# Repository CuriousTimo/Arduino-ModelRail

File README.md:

# Code for all kinds of LocoNet and DCC devices using an Arduino

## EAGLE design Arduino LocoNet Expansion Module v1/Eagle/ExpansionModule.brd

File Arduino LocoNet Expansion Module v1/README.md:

# Arduino LocoNet Expansion Module v1

A general-purpose expansion for the [Arduino Nano LocoNet & DCC Interface v3](../Arduino%20LocoNet-DCC%20Interface%20v3) (or a v2 with the [v2 Expansion Adapter](../Arduino%20LocoNet-DCC%20v2%20Expansion%20Adapter)). It connects with two 10-pin flat cables to **EXP1** and **EXP2** and brings sixteen Nano pins out to screw terminals, **P1 to P16**, plus 5 V and GND terminals.

The board is made for different setups: **you only fit the parts your project needs**, chosen per terminal. A terminal can be a plain connection to the Nano pin (for an output, a button, a servo signal) or a protected input (for Märklin contact tracks or reed contacts), and one board can mix both.

Designed in EAGLE 9.6.2: the schematic and the board are in [`Eagle/`](Eagle), the Gerber files (31 January 2021) for ordering the board in [`Gerber/`](Gerber). Board 65.7 × 83.8 mm, two layers, through-hole parts only.

*The board from above, drawn from the EAGLE file: red tracks on top, blue underneath, green pads, grey the printing on the board.*

## Fitting the board for your task

Every terminal has the same places for parts. Choose for each terminal:

| Use | Fit | Leave empty |
| --- | --- | --- |
| **Plain connection**: an output (an LED with its own resistor, a servo signal), a sensor with a 5 V output | Jumper **JP** closed, or a wire bridge in its place | R, 1N4148, 1N4004, C |
| **Switch input**: a push button, toggle switch, reed contact or turnout end switch to GND | 1 kΩ **R**, **1N4148**, **1N4004**, **C** | JP (open) |
| **3-rail feedback**: a Märklin contact track (isolated outer rail), also with a DCC command station such as the Intellibox | 1 kΩ **R**, **1N4148**, **1N4004**, **C** | JP (open) |
| **Not used** | Nothing | Everything |

Fit the **terminals** you use and the **EXP** headers for the cables you need: EXP1 for P1 to P8, EXP2 for P9 to P16. The 5V and GND terminals only when something needs power from the board.

## Switch input and 3-rail feedback

Both use the same parts, and one board can have both. The full circuit of one terminal, with all its parts fitted:

```text
 Nano pin ──┬── 1 kΩ ──▶|── 1N4148 ──┬── terminal P
            │                         │
           C                       1N4004
            │                       (▲ to GND)
           GND                        │
                                     GND
     and jumper JP: Nano pin ── terminal P (bypasses the resistor and diode)
```

- The Nano pin is an input with its **internal pull-up** switched on (`pinMode(pin, INPUT_PULLUP)`).
- **Nothing connected, or the contact open:** the pin reads **HIGH**.
- **Terminal connected to GND** (a pressed button, a closed reed contact): current flows through the 1 kΩ and the 1N4148, and the pin reads **LOW**.
- **The 1N4148** keeps positive voltages on the terminal away from the Nano, for example when a wire touches the track or the 16 V lighting supply.
- **The 1N4004** takes negative voltages on the terminal to GND.
- **The capacitor** filters short spikes and contact bounce. Its value is not in the design; 100 nF is the usual choice.

### Switch input

Connect the switch between the terminal and a **GND** terminal. Closed is LOW, open is HIGH.

### 3-rail feedback with the diode trick

On a Märklin contact track, one outer rail is cut on both sides of the section and wired to the terminal. A train's metal wheels connect it to the other outer rail.

- **With a Märklin system** (the outer rails are the track's ground, brown "0") and the board's GND connected to that ground, it works like a switch: a train pulls the terminal to GND, and the pin reads LOW.
- **With a DCC command station or booster** (such as the Intellibox), the outer rails are not ground: they switch between 0 V and the full track voltage thousands of times a second. This is where the **diode trick** comes in:
  - In the half where the rail is at 0 V, the 1N4148 conducts and pulls the pin LOW.
  - In the half where the rail is at track voltage, the 1N4148 blocks, so the Nano never sees the track voltage.
  - The capacitor holds the pin LOW until the next 0 V half, so the pin stays LOW as long as a train is on the section.
  
  The board's GND must share a ground with the command station; through LocoNet it normally does. Test one section with a loco before wiring the whole layout.

Dirty wheels and track make the contact flicker. Let the program wait about half a second after the last LOW before it reports the section as free.

**Jumper JP1 to JP16** (one per terminal, next to it) connects the Nano pin straight to the terminal, without the protection: the plain connection. Then the terminal is not protected, so never more than 5 V on it, and leave the capacitor out on outputs (it would slow down a servo signal).

## Terminals and Nano pins

| Terminal | Nano pin | Flat cable | | Terminal | Nano pin | Flat cable |
| --- | --- | --- | --- | --- | --- | --- |
| P1 | D2 | EXP1 pin 1 | | P9 | D12 | EXP2 pin 1 |
| P2 | D3 | EXP1 pin 2 | | P10 | D13 | EXP2 pin 2 |
| P3 | D4 | EXP1 pin 3 | | P11 | A0 | EXP2 pin 3 |
| P4 | D5 | EXP1 pin 4 | | P12 | A1 | EXP2 pin 4 |
| P5 | D6 | EXP1 pin 5 | | P13 | A2 | EXP2 pin 5 |
| P6 | D9 | EXP1 pin 6 | | P14 | A3 | EXP2 pin 6 |
| P7 | D10 | EXP1 pin 7 | | P15 | SDA (A4) | EXP2 pin 7 |
| P8 | D11 | EXP1 pin 8 | | P16 | SCL (A5) | EXP2 pin 8 |

Pins 9 and 10 of both flat cables are 5 V and GND. The two **5V** and two **GND** terminals on the left (top and bottom) carry them, for example to power IR or Hall sensors.

Some inputs share their Nano pin with something on the interface board:

| Terminal | Shared with | What to do |
| --- | --- | --- |
| **P1** (D2) | The DCC input | Leave P1 unused when the interface's DCC part (6N137) is fitted |
| **P4, P5** (D5, D6) | The interface's blue terminal, when its SCL/SDA jumpers are on the right | Put those jumpers on the left, or leave the blue terminal's D5/D6 unused |
| **P10** (D13) | The Nano's own LED on D13 | The LED pulls the pin down, so the pull-up does not work reliably; use P10 as an output, or leave it unused |
| **P15, P16** (A4, A5) | I2C | Not available as inputs when I2C is used (a PCA9685, the Märklin I2C Expansion). The interface's "i2c pullup" jumper may stay on; it only makes the pull-up stronger |

D0, D1 (USB) and D7, D8 (LocoNet) are not on the flat cables.

## Parts list

Fit only what you need (see [Fitting the board for your task](#fitting-the-board-for-your-task)). Per terminal:

| Part | Value | For |
| --- | --- | --- |
| R | 1 kΩ | Protected input |
| D (small glass diode) | 1N4148 | Protected input |
| D (larger black diode) | 1N4004 | Protected input |
| C | 100 nF (value not in the design), 5 mm pin spacing | Protected input |
| JP | 2-pin header and a jumper, or a wire bridge | Plain connection |

For the board:

| Part | Value | Number |
| --- | --- | --- |
| PORT1 to PORT8 | 2-pole terminal, 5.08 mm (each holds two terminals, for example P1 and P2) | 1 to 8, as needed |
| 5V-L, 5V-R, GND-L, GND-R | 2-pole terminal, 5.08 mm | As needed |
| EXP1, EXP2 | 10-pin boxed header (2 × 5, 2.54 mm) | 1 or 2 |
| | 10-pin flat cable with two connectors | 1 or 2 |

A board with all sixteen protected inputs needs 16 of each: R1 to R16, sixteen 1N4148, sixteen 1N4004 and C1 to C16.

## Software

No program in this repository uses the module yet. Reading an input in an Arduino sketch:

```cpp
const uint8_t kInputs[16] = {2, 3, 4, 5, 6, 9, 10, 11, 12, 13, A0, A1, A2, A3, A4, A5};  // P1 to P16

void setup() {
  for (uint8_t pin : kInputs) pinMode(pin, INPUT_PULLUP);
}

void loop() {
  bool occupied = digitalRead(kInputs[2]) == LOW;  // P3: LOW when the contact is closed
}
```

To report the inputs on LocoNet, send an `OPC_INPUT_REP` (sensor message) when an input changes, as LocoNet occupancy detectors do.

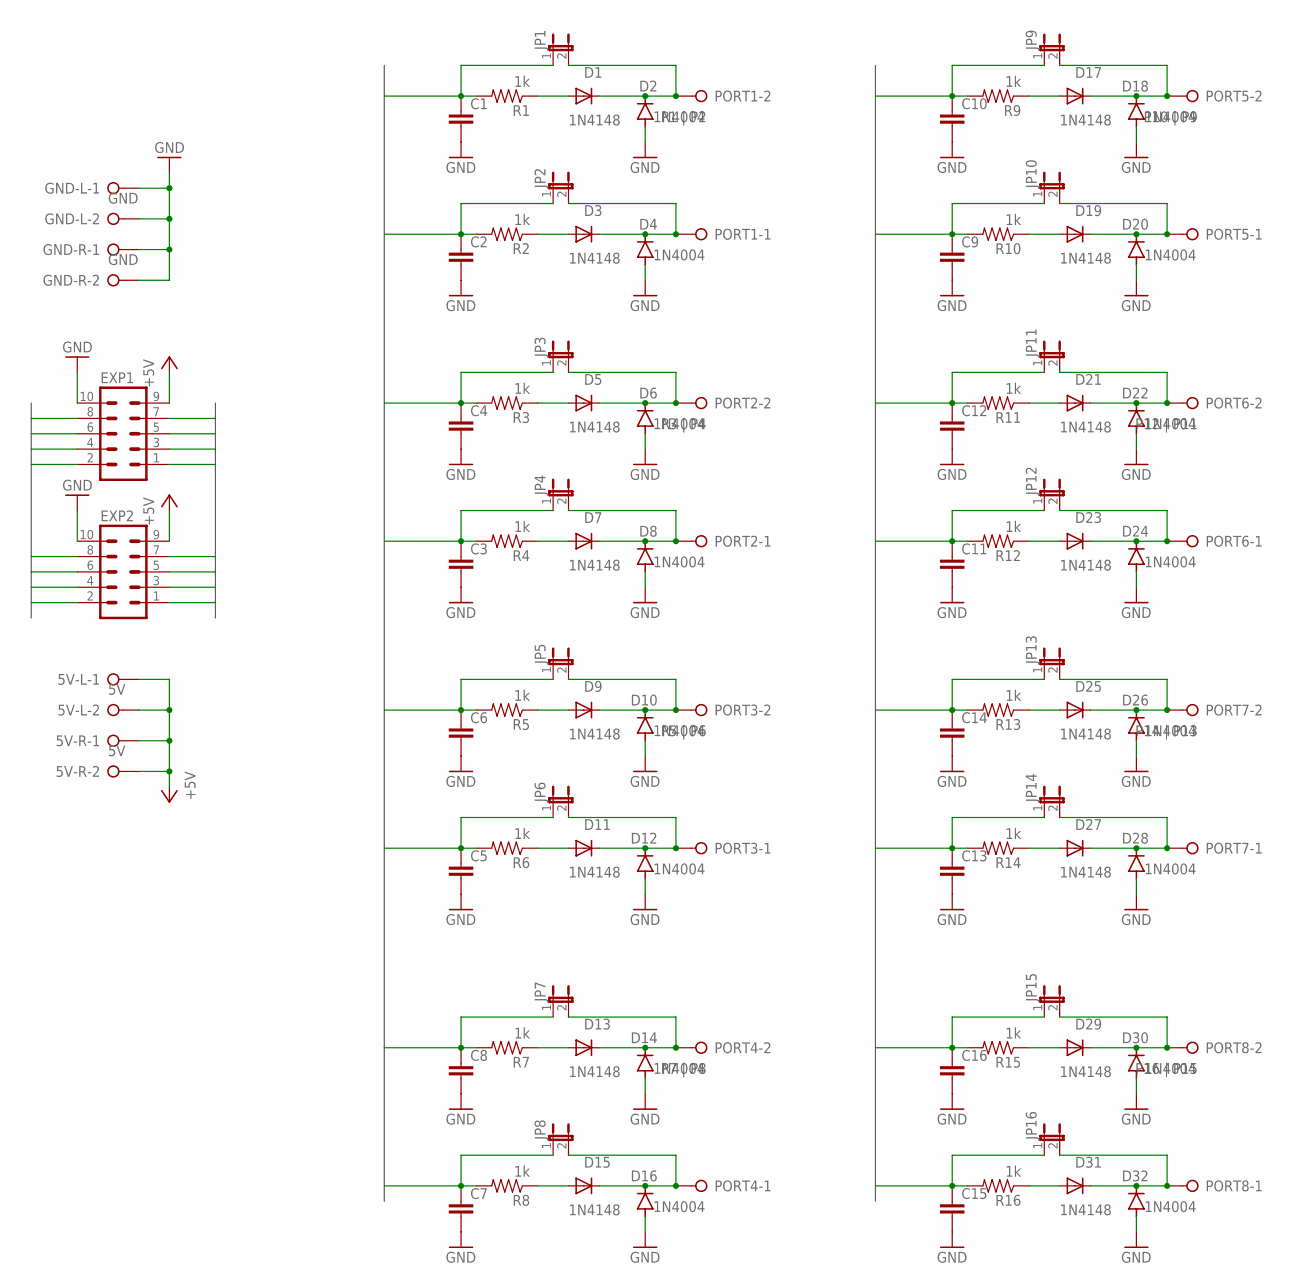
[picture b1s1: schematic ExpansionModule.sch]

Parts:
5V-L, 5V-R: 5V; W237-132
C1, C2, C3, C4, C5, C6, C7, C8, C9, C10, C11, C12, C13, C14, C15, C16: C-EU050-030X075; C050-030X075
D1, D3, D5, D7, D9, D11, D13, D15, D17, D19, D21, D23, D25, D27, D29, D31: 1N4148; DO35-7
D2, D4, D6, D8, D10, D12, D14, D16, D18, D20, D22, D24, D26, D28, D30, D32: 1N4004; DO41-10
EXP1, EXP2: ML10
GND-L: GND; W237-132
GND-R: GND; W237-132
JP1, JP2, JP3, JP4, JP5, JP6, JP7, JP8, JP9, JP10, JP11, JP12, JP13, JP14, JP15, JP16: JP1E; JP1
PORT1: P1 | P2; W237-132
PORT2: P3 | P4; W237-132
PORT3: P5 | P6; W237-132
PORT4: P7 | P8; W237-132
PORT5: P10 | P9; W237-132
PORT6: P12 | P11; W237-132
PORT7: P14 | P13; W237-132
PORT8: P16 | P15; W237-132
R1, R2, R3, R4, R5, R6, R7, R8, R9, R10, R11, R12, R13, R14, R15, R16: 1k; AXIAL-0.3

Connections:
+5V: 5V-L.1, 5V-L.2, 5V-R.1, 5V-R.2, EXP1.9, EXP2.9
A0: C12.1, EXP2.3, JP11.1, R11.P$2 (2)
A1: C11.1, EXP2.4, JP12.1, R12.P$2 (2)
A2: C14.1, EXP2.5, JP13.1, R13.P$2 (2)
A3: C13.1, EXP2.6, JP14.1, R14.P$2 (2)
GND: C1.2, C2.2, C3.2, C4.2, C5.2, C6.2, C7.2, C8.2, C9.2, C10.2, C11.2, C12.2, C13.2, C14.2, C15.2, C16.2, D2.A, D4.A, D6.A, D8.A, D10.A, D12.A, D14.A, D16.A, D18.A, D20.A, D22.A, D24.A, D26.A, D28.A, D30.A, D32.A, EXP1.10, EXP2.10, GND-L.1, GND-L.2, GND-R.1, GND-R.2
unnamed: D1.A, R1.P$1 (1)
unnamed: D3.A, R2.P$1 (1)
unnamed: D5.A, R3.P$1 (1)
unnamed: D7.A, R4.P$1 (1)
unnamed: D9.A, R5.P$1 (1)
unnamed: D11.A, R6.P$1 (1)
unnamed: D13.A, R7.P$1 (1)
unnamed: D15.A, R8.P$1 (1)
unnamed: D17.A, R9.P$1 (1)
unnamed: D19.A, R10.P$1 (1)
unnamed: D21.A, R11.P$1 (1)
unnamed: D23.A, R12.P$1 (1)
unnamed: D25.A, R13.P$1 (1)
unnamed: D27.A, R14.P$1 (1)
unnamed: D29.A, R15.P$1 (1)
unnamed: D31.A, R16.P$1 (1)
PIN2: C1.1, EXP1.1, JP1.1, R1.P$2 (2)
PIN3: C2.1, EXP1.2, JP2.1, R2.P$2 (2)
PIN4: C4.1, EXP1.3, JP3.1, R3.P$2 (2)
PIN5: C3.1, EXP1.4, JP4.1, R4.P$2 (2)
PIN6: C6.1, EXP1.5, JP5.1, R5.P$2 (2)
PIN9: C5.1, EXP1.6, JP6.1, R6.P$2 (2)
PIN10: C8.1, EXP1.7, JP7.1, R7.P$2 (2)
PIN11: C7.1, EXP1.8, JP8.1, R8.P$2 (2)
PIN12: C10.1, EXP2.1, JP9.1, R9.P$2 (2)
PIN13: C9.1, EXP2.2, JP10.1, R10.P$2 (2)
PORT1: D1.C, D2.C, JP1.2, PORT1.2
PORT2: D3.C, D4.C, JP2.2, PORT1.1
PORT3: D5.C, D6.C, JP3.2, PORT2.2
PORT4: D7.C, D8.C, JP4.2, PORT2.1
PORT5: D9.C, D10.C, JP5.2, PORT3.2
PORT6: D11.C, D12.C, JP6.2, PORT3.1
PORT7: D13.C, D14.C, JP7.2, PORT4.2
PORT8: D15.C, D16.C, JP8.2, PORT4.1
PORT9: D17.C, D18.C, JP9.2, PORT5.2
PORT10: D19.C, D20.C, JP10.2, PORT5.1
PORT11: D21.C, D22.C, JP11.2, PORT6.2
PORT12: D23.C, D24.C, JP12.2, PORT6.1
PORT13: D25.C, D26.C, JP13.2, PORT7.2
PORT14: D27.C, D28.C, JP14.2, PORT7.1
PORT15: D29.C, D30.C, JP15.2, PORT8.2
PORT16: D31.C, D32.C, JP16.2, PORT8.1
SCL: C15.1, EXP2.8, JP16.1, R16.P$2 (2)
SDA: C16.1, EXP2.7, JP15.1, R15.P$2 (2)

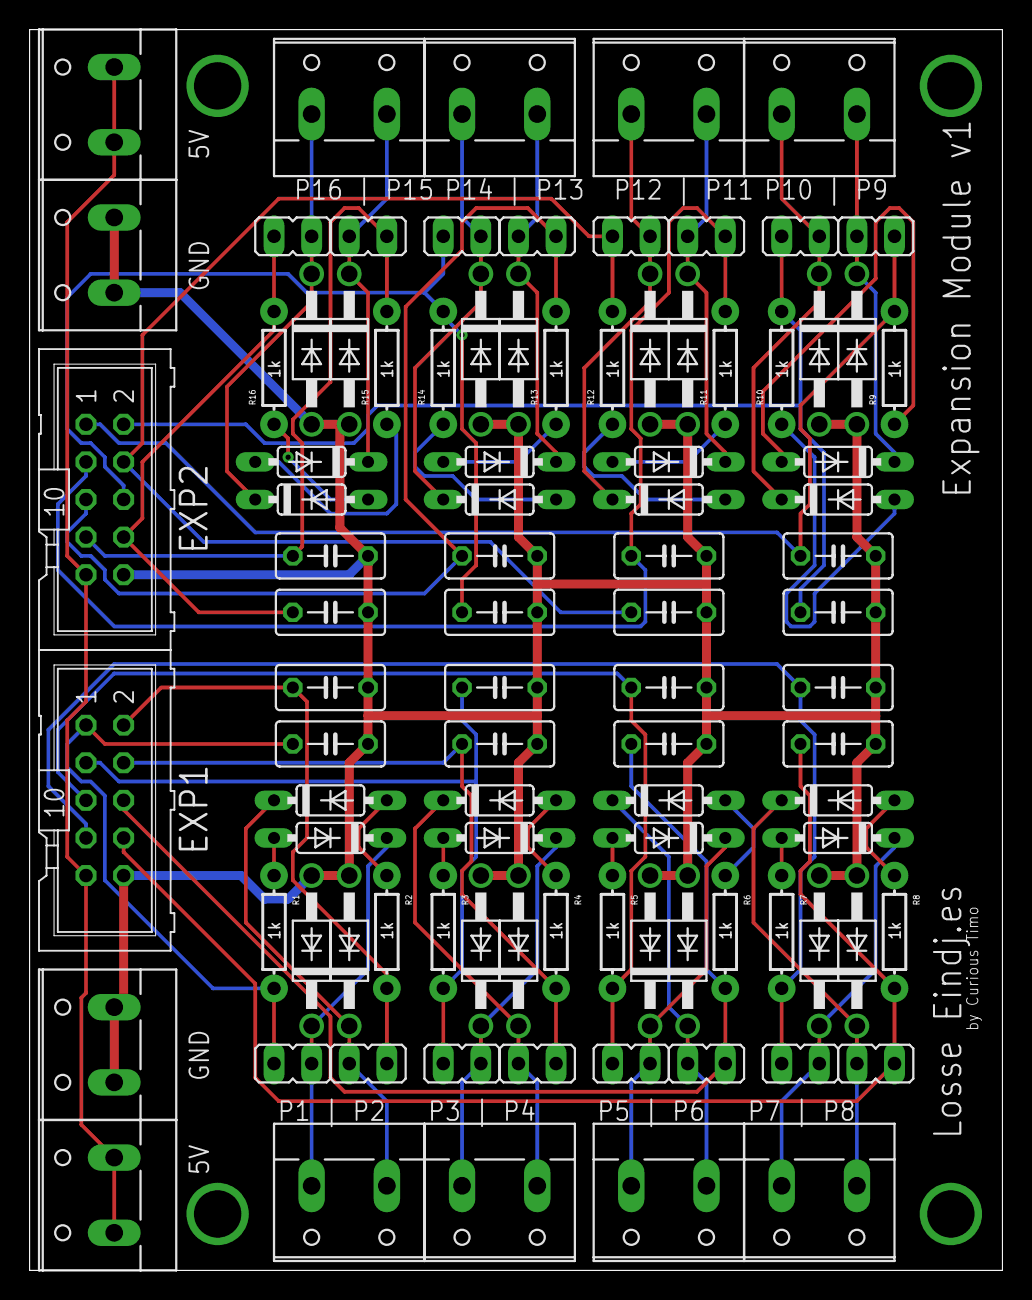
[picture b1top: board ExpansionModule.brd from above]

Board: 2 copper layers, 65.7 x 83.8 mm, 94 parts (0 on the bottom side), 50 nets.

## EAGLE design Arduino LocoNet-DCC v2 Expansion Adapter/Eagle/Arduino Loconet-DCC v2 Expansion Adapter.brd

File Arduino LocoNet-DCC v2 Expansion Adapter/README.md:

# Arduino LocoNet-DCC v2 Expansion Adapter

Gives an [Arduino Nano LocoNet & DCC Interface v2](../Arduino%20LocoNet-DCC%20Interface%20v2) the two expansion headers of the [v3](../Arduino%20LocoNet-DCC%20Interface%20v3), **EXP1** and **EXP2**, so expansion boards made for the v3 work on a v2 with the same 10-pin flat cable, for example the [Märklin I2C Expansion v1](../Marklin%20I2C%20Expansion%20v1) for [Marklin-6040-LocoNet](../Marklin-6040-LocoNet).

Designed in EAGLE 9.6.2: the schematic and the board are in [`Eagle/`](Eagle). Board 42.9 × 30.5 mm, two layers.

*The board from above, drawn from the EAGLE file: red tracks on top, blue underneath, green pads, grey the printing on the board.*

## How it fits

The adapter sits between the v2 board and the Arduino Nano:

1. Solder two **15-pin stackable headers** into the adapter (sockets on top, long pins underneath), and the two 10-pin headers EXP1 and EXP2.
2. Plug the adapter into the v2's Nano sockets, with the "<-Arduino USB" marking on the same side as the v2's.
3. Plug the Nano into the adapter.

Every Nano pin reaches the v2 board through the long pins; the adapter only takes the pins below off to the expansion headers. LocoNet (D7, D8) and the serial port (D0, D1) are not on the headers and stay free for the v2.

## Expansion headers

Wired exactly as on the v3, so a flat cable fits either board:

| Pin | EXP1 | EXP2 |
| --- | --- | --- |
| 1 | D2 (DCC input) | D12 |
| 2 | D3 | D13 |
| 3 | D4 | A0 |
| 4 | D5 | A1 |
| 5 | D6 | A2 |
| 6 | D9 | A3 |
| 7 | D10 | SDA (A4) |
| 8 | D11 | SCL (A5) |
| 9 | 5 V | 5 V |
| 10 | GND | GND |

D5 and D6 are also on the v2's blue terminal when its SCL/SDA jumpers are on the right, and SDA and SCL when they are on the left (see the [v2 jumpers](../Arduino%20LocoNet-DCC%20Interface%20v2#jumpers)); don't use the same pin on both.

## With the Märklin I2C Expansion

Connect the expansion to **EXP2**, and on the v2 put the **i2c pullup** jumper on (the Keyboard bus needs it). The rest is as described for the [Märklin I2C Expansion](../Marklin%20I2C%20Expansion%20v1).

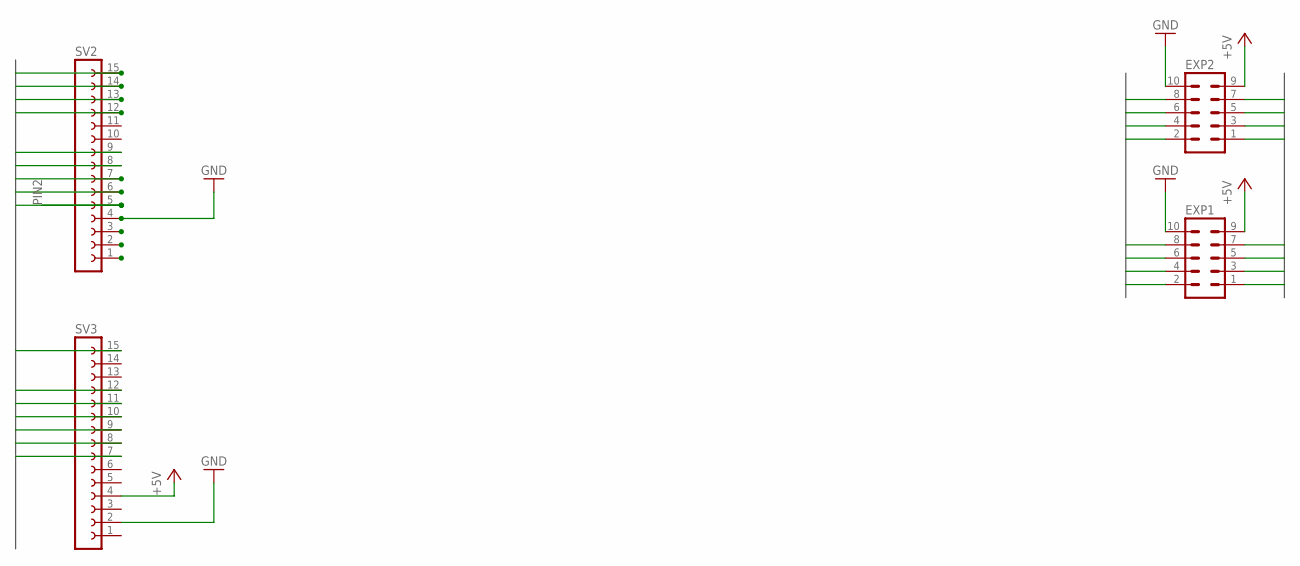
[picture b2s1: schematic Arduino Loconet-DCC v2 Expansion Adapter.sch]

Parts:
EXP1, EXP2: ML10
SV2, SV3: FE15-1NOTEXT; FE15

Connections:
+5V: EXP1.9, EXP2.9, SV3.4
A0: EXP2.3, SV3.12
A1: EXP2.4, SV3.11
A2: EXP2.5, SV3.10
A3: EXP2.6, SV3.9
GND: EXP1.10, EXP2.10, SV2.4, SV3.2
PIN2: EXP1.1, SV2.5
PIN3: EXP1.2, SV2.6
PIN4: EXP1.3, SV2.7
PIN5: EXP1.4, SV2.8
PIN6: EXP1.5, SV2.9
PIN9: EXP1.6, SV2.12
PIN10: EXP1.7, SV2.13
PIN11: EXP1.8, SV2.14
PIN12: EXP2.1, SV2.15
PIN13: EXP2.2, SV3.15
RESET: SV2.3
RXD: SV2.2
SCL: EXP2.8, SV3.7
SDA: EXP2.7, SV3.8
TXD: SV2.1

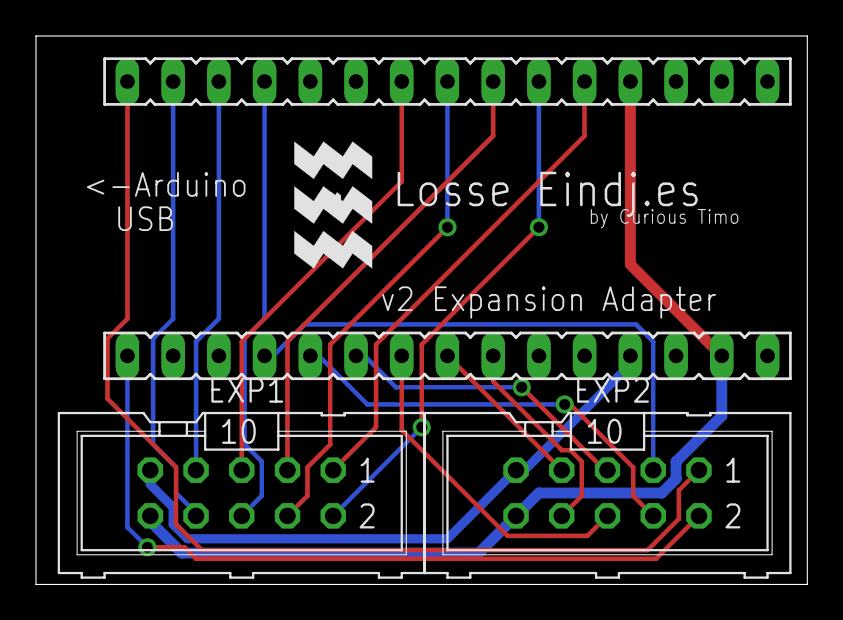
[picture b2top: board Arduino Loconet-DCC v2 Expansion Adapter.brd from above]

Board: 2 copper layers, 42.9 x 30.5 mm, 4 parts (0 on the bottom side), 18 nets.

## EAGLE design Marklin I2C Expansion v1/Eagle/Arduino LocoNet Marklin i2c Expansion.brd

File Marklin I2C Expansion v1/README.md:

# Märklin I2C Expansion v1

An expansion for the [Arduino Nano LocoNet & DCC Interface v3](../Arduino%20LocoNet-DCC%20Interface%20v3) (or a v2 with the [v2 Expansion Adapter](../Arduino%20LocoNet-DCC%20v2%20Expansion%20Adapter)) that connects Märklin Keyboards 6040 (the Märklin Digital accessory bus, I2C) to the Nano. Used by [Marklin-6040-LocoNet](../Marklin-6040-LocoNet), which makes unmodified Keyboards 6040 work on LocoNet like an Uhlenbrock IB-Switch.

Designed in EAGLE 9.6.2: the schematic and the board are in [`Eagle/`](Eagle). Board 44.8 × 61 mm, two layers.

*The board from above, drawn from the EAGLE file: red tracks on top, blue underneath, green pads, grey the printing on the board.*

## On the board

- **Two DIN 41612 connectors** (left and right, 32-pole B/2), for the Keyboards' side connectors: SDA, SCL, STOP, GO, INIT and 8 V. The left and right connectors are mirrored, so a Keyboard fits on either side, and further Keyboards plug onto each other as usual.
- **XL6009 step-up converter** that makes the Keyboards' 8 V, through a 1N4004 diode.
- **10-pin ribbon cable** to the interface board's **EXP2**: STOP to D12, GO to A0, INIT to A1, a red LED to D13, SDA and SCL to A4 and A5, plus 5 V and GND.
- **DC-IN** two-pole terminal and jumper **JP1**.

## Before switching on

1. Close the **"i2c pullup"** jumper on the interface board: the Keyboard bus needs pull-ups to 5 V.
2. Feed **DC-IN with 5 V** and leave **JP1 open**. Each Keyboard draws about 120 mA at 8 V, which is too much for the interface board's 7805 or for LocoNet.
3. **Never more than 5 V on DC-IN with JP1 closed:** JP1 connects DC-IN to the Nano's 5 V.
4. Give every Keyboard its own number with the four switches on its back (see the table in the [Marklin-6040-LocoNet README](../Marklin-6040-LocoNet#setting-up)).

## To check before building more

- **STOP, GO and INIT** go straight to Nano pins. Measure their voltage on a Keyboard bus before using them (the firmware leaves STOP and GO switched off until then).
- **JP1** connects DC-IN to the Nano's 5 V without protection; a marking on the board ("5 V only") or a diode would help.

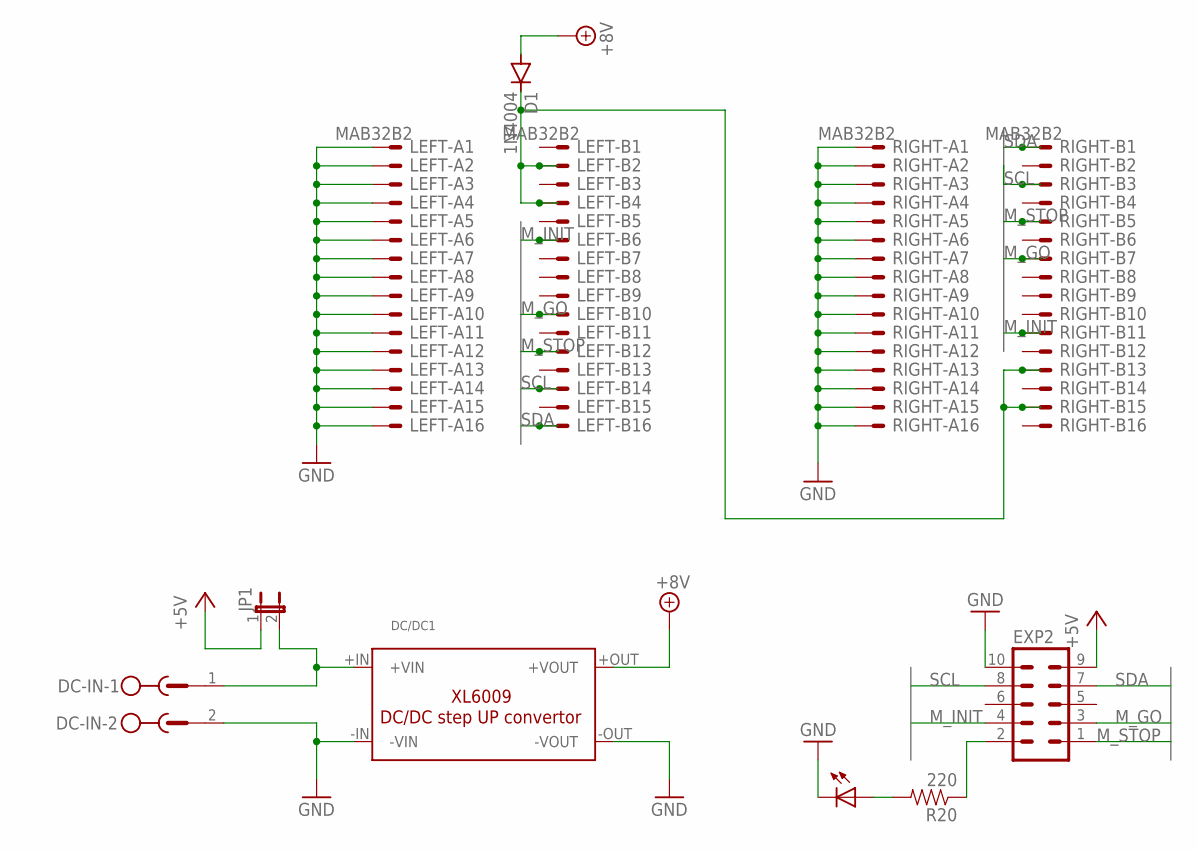
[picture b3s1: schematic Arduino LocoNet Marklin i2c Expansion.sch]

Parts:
D1: 1N4004; DO41-10
DC-IN: 2EDG-02
DC/DC1: DC/DC-STEP-UP-XL6009
EXP2: ML10
JP1: JP1E; JP1
LED: RED; LED3MM
LEFT: MAB32B2
R20: 220; AXIAL-0.3
RIGHT: MAB32B2

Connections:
+5V: EXP2.9, JP1.1
+8V: D1.A, DC/DC1.+OUT (+VOUT)
DC+: DC-IN.1, DC/DC1.+IN (+VIN), JP1.2
GND: DC-IN.2, DC/DC1.-IN (-VIN), DC/DC1.-OUT (-VOUT), EXP2.10, LED.K (C), LEFT.A1, LEFT.A2, LEFT.A3, LEFT.A4, LEFT.A5, LEFT.A6, LEFT.A7, LEFT.A8, LEFT.A9, LEFT.A10, LEFT.A11, LEFT.A12, LEFT.A13, LEFT.A14, LEFT.A15, LEFT.A16, RIGHT.A1, RIGHT.A2, RIGHT.A3, RIGHT.A4, RIGHT.A5, RIGHT.A6, RIGHT.A7, RIGHT.A8, RIGHT.A9, RIGHT.A10, RIGHT.A11, RIGHT.A12, RIGHT.A13, RIGHT.A14, RIGHT.A15, RIGHT.A16
M_GO: EXP2.3, LEFT.B10, RIGHT.B7
M_INIT: EXP2.4, LEFT.B6, RIGHT.B11
M_STOP: EXP2.1, LEFT.B12, RIGHT.B5
unnamed: LED.A, R20.P$2 (2)
unnamed: D1.C, LEFT.B2, LEFT.B4, RIGHT.B13, RIGHT.B15
PIN13: EXP2.2, R20.P$1 (1)
SCL: EXP2.8, LEFT.B14, RIGHT.B3
SDA: EXP2.7, LEFT.B16, RIGHT.B1

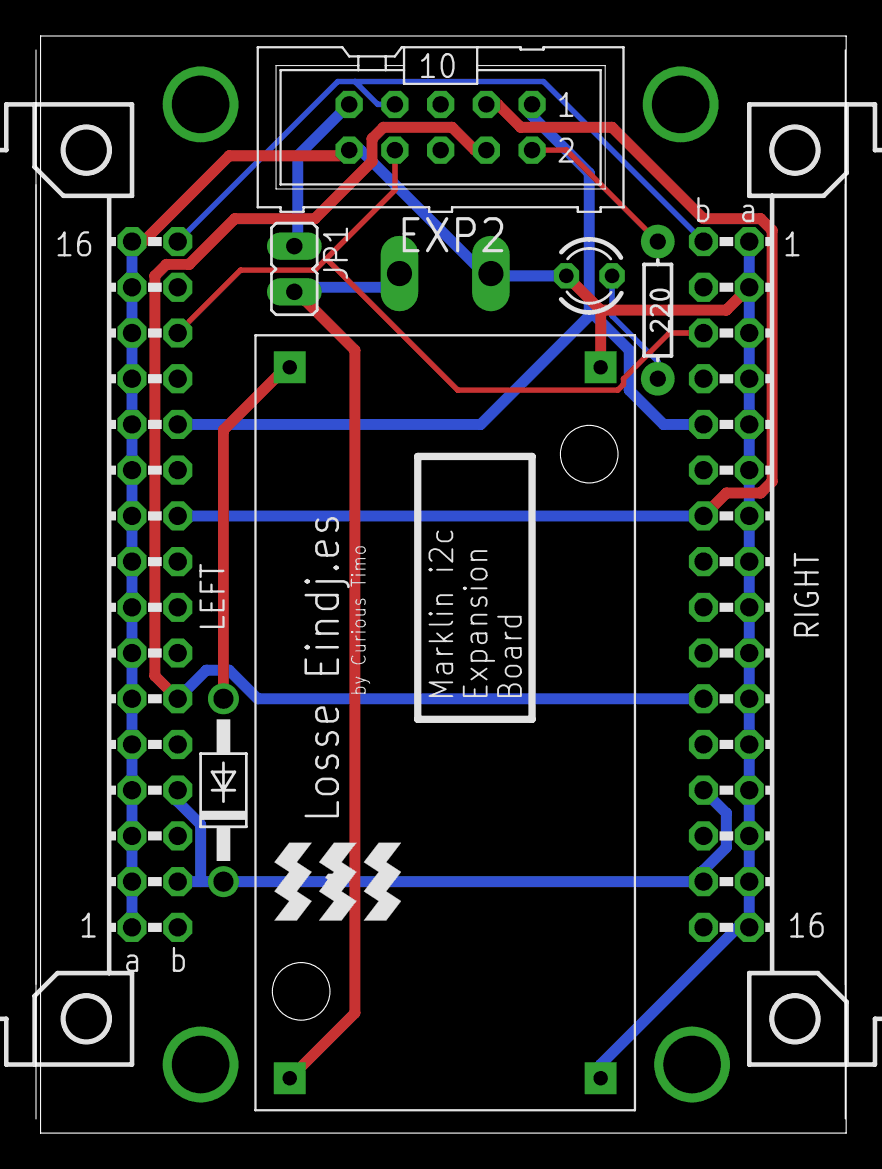
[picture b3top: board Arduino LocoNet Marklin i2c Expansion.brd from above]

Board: 2 copper layers, 44.8 x 61.0 mm, 9 parts (1 on the bottom side), 12 nets.

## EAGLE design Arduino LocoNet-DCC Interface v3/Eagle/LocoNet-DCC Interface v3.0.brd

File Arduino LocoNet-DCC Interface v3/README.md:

# Arduino Nano LocoNet & DCC Interface v3

The base module for LocoNet projects with an Arduino Nano: LocoNet in and out, a DCC input, I2C for servo drivers and expansion boards, and two expansion headers. It is the successor of the [v2](../Arduino%20LocoNet-DCC%20Interface%20v2) and the base of [Marklin-6040-LocoNet](../Marklin-6040-LocoNet), together with the [Märklin I2C Expansion v1](../Marklin%20I2C%20Expansion%20v1).

Designed in EAGLE 9.6.2: the schematic and the board are in [`Eagle/`](Eagle). Board 108.9 × 47 mm, two layers, through-hole parts only.

*The board from above, drawn from the EAGLE file: red tracks on top, blue underneath, green pads, grey the printing on the board.*

## On the board

| Part | What it does | Nano pin |
| --- | --- | --- |
| 2 × LocoNet socket (RJ12) | LocoNet in and out, wired straight through | |
| LocoNet receive | LM393 comparator: switches at about 4.5 V rising and 3.5 V falling on the LocoNet line; red LED shows LocoNet traffic | **D8** (the input-capture pin the LocoNet library needs) |
| LocoNet send | BC337 transistor that pulls the LocoNet line low | **D7** |
| DCC input | 6N137 optocoupler, DCC from the track or a booster on the two-pole terminal | **D2** (interrupt, as NmraDcc needs) |
| Power | 7805 regulator, fed from LocoNet RailSync or a separate power input (both through diodes); green LED | |
| I2C | 4.7 kΩ pull-ups (jumper), a 6-pin header for a PCA9685 servo board | A4 (SDA), A5 (SCL) |
| Blue 4-pole terminal | 5V · SCL/D5 · SDA/D6 · GND: either I2C or D5/D6, chosen with jumpers | |
| Power terminal (PWR +, GND) | A separate supply for the 7805, about 9 to 15 V DC | |
| DCC terminal | DCC from the track or a booster; the way round does not matter | |
| EXP1 (10-pin) | D2 (DCC), D3, D4, D5, D6, D9, D10, D11, 5 V, GND | |
| EXP2 (10-pin) | D12, D13, A0, A1, A2, A3, SDA, SCL, 5 V, GND; the Märklin I2C Expansion connects here | |

Expansion boards for EXP1 and EXP2: the [Märklin I2C Expansion v1](../Marklin%20I2C%20Expansion%20v1) and the [Expansion Module v1](../Arduino%20LocoNet%20Expansion%20Module%20v1) (16 terminals, as protected inputs or plain connections).

## Jumpers

The jumpers are the same as on the [v2](../Arduino%20LocoNet-DCC%20Interface%20v2#jumpers), at the same place: bottom left, next to the Nano's USB socket, with their names printed on the board.

### Power and pull-ups: three jumpers in a row

A jumper is placed **upright**, on the two pins of one column.

```text
        5V from      Vin from      i2c
         7805        Loconet      pullup
        ┌─────┐      ┌─────┐      ┌─────┐
        │  ●  │      │  ●  │      │  ●  │
        │  ●  │      │  ●  │      │  ●  │
        └─────┘      └─────┘      └─────┘
```

| Jumper | When it is on | Put it on when |
| --- | --- | --- |
| **5V from 7805** | The board's 7805 regulator powers the Nano's 5 V | The board gets its power from LocoNet or the power terminal, and the 7805 is fitted. **This is the usual setting.** |
| **Vin from Loconet** | LocoNet's RailSync and the power terminal (each through a diode) go to the Nano's VIN pin, so the Nano's own small regulator makes the 5 V | The 7805 is **not** fitted. Use this one *or* "5V from 7805", not both |
| **i2c pullup** | The two 4.7 kΩ pull-up resistors on SDA and SCL are connected to 5 V | I2C devices are connected that have no pull-ups of their own. **On for the Märklin I2C Expansion** (the Keyboard bus needs it) |

With only the USB cable connected, the jumpers can stay as they are: a diode across the 7805 protects it.

**For [Marklin-6040-LocoNet](../Marklin-6040-LocoNet):** *5V from 7805* on, *Vin from Loconet* off, *i2c pullup* on. Power the Keyboards through the expansion board's own DC-IN, not through this board.

### Blue 4-pole terminal: I2C or D5/D6

Two rows of three pins. The middle column goes to the blue terminal; always put **both jumpers on the same side**.

```text
  I2C on the blue terminal             D5 and D6 on the blue terminal

  SCL  ●━━━●  ○  D5                    SCL  ○  ●━━━●  D5
  SDA  ●━━━●  ○  D6                    SDA  ○  ●━━━●  D6
```

| Setting | Terminal "SCL/D5" | Terminal "SDA/D6" |
| --- | --- | --- |
| Both jumpers **left** | SCL (A5) | SDA (A4) |
| Both jumpers **right** | D5 | D6 |

## Parts list

Fit only the groups you need. The names are the ones on the board and in the schematic.

| Group | Part | Value |
| --- | --- | --- |
| **Power supply** | VR1 | LM7805 |
| | R20 | 2.2 kΩ (power LED) |
| | D1 | 1N4003 (protects the 7805) |
| | D5 | 1N4004 (power terminal) |
| | C1, C3 | 100 nF |
| | C2 | 10 µF |
| | POWER | 3 mm green LED |
| | PWR | 2-pole terminal, 5.08 mm |
| **I2C** | R9, R10 | 4.7 kΩ |
| | PCA9685 | 6-pin male header, for a PCA9685 servo board |
| | X1 | 4-pole terminal, 5.08 mm (the blue terminal) |
| **LocoNet** | IC1 | LM393N comparator |
| | T1 | BC337 NPN transistor |
| | R1 | 4.7 kΩ |
| | R2 | 27 kΩ |
| | R3 | 39 kΩ |
| | R4 | 47 kΩ |
| | R5 | 150 kΩ |
| | R6 | 240 kΩ |
| | R7 | 1 kΩ |
| | R8 | 470 Ω (LocoNet LED) |
| | D2, D3 | 1N4003 (RailSync to the power supply) |
| | LOCONET | 3 mm red LED |
| | J1, J2 | 6-pin modular sockets (RJ12) |
| **DCC** | DCC | 6N137 optocoupler |
| | R11, R12, R13 | 10 kΩ (R13: see below) |
| | D4 | 1N4148 |
| | DCC-IN | 2-pole terminal, 5.08 mm |
| **Nano and headers** | SV2, SV3 | 2 × 15-pin female header, for the Arduino Nano |
| | SV1, SDA | 2 × 15-pin female header next to the Nano, with every Nano pin (optional) |
| | EXP1, EXP2 | 2 × 10-pin boxed header (2 × 5, 2.54 mm), for the expansion flat cables |
| | JP1 | 2 × 3 pin header and 3 jumpers (power and pull-ups) |
| | SCL/SDA | 2 × 3 pin header and 2 jumpers (blue terminal) |
| | | Arduino Nano (ATmega328P, 5 V) |

The 6N137 and the LM393N are easier to replace in an 8-pin IC socket. R13 limits the current through the optocoupler: at 10 kΩ it gives about 1.5 mA at 16 V DCC, while a 6N137 is only guaranteed to switch at about 5 mA; if DCC is not detected reliably, **1.5 to 2.2 kΩ** (0.25 W) is the safer value.

## To check before building more

Points from a review of the v3 design; none of them stops the board from working on the bench, but they are worth looking at for a v4:

- **DCC optocoupler resistor:** 10 kΩ gives about 1.5 mA at 16 V DCC, while a 6N137 is only guaranteed to switch at about 5 mA. 1.5 to 2.2 kΩ (0.25 W) is safer.
- **Unused half of the LM393:** both inputs on GND can let its output oscillate; one input to the reference voltage is the usual fix.
- **Comparator output load:** the 1 kΩ pull-up and the 470 Ω LED together draw about 11 mA from the LM393's output, at the upper end of what it does comfortably.
- **No protection** (TVS diode or polyfuse) on LocoNet.
- **Power budget:** the 7805 runs warm when it also has to feed expansion boards; heavy loads are better fed separately.

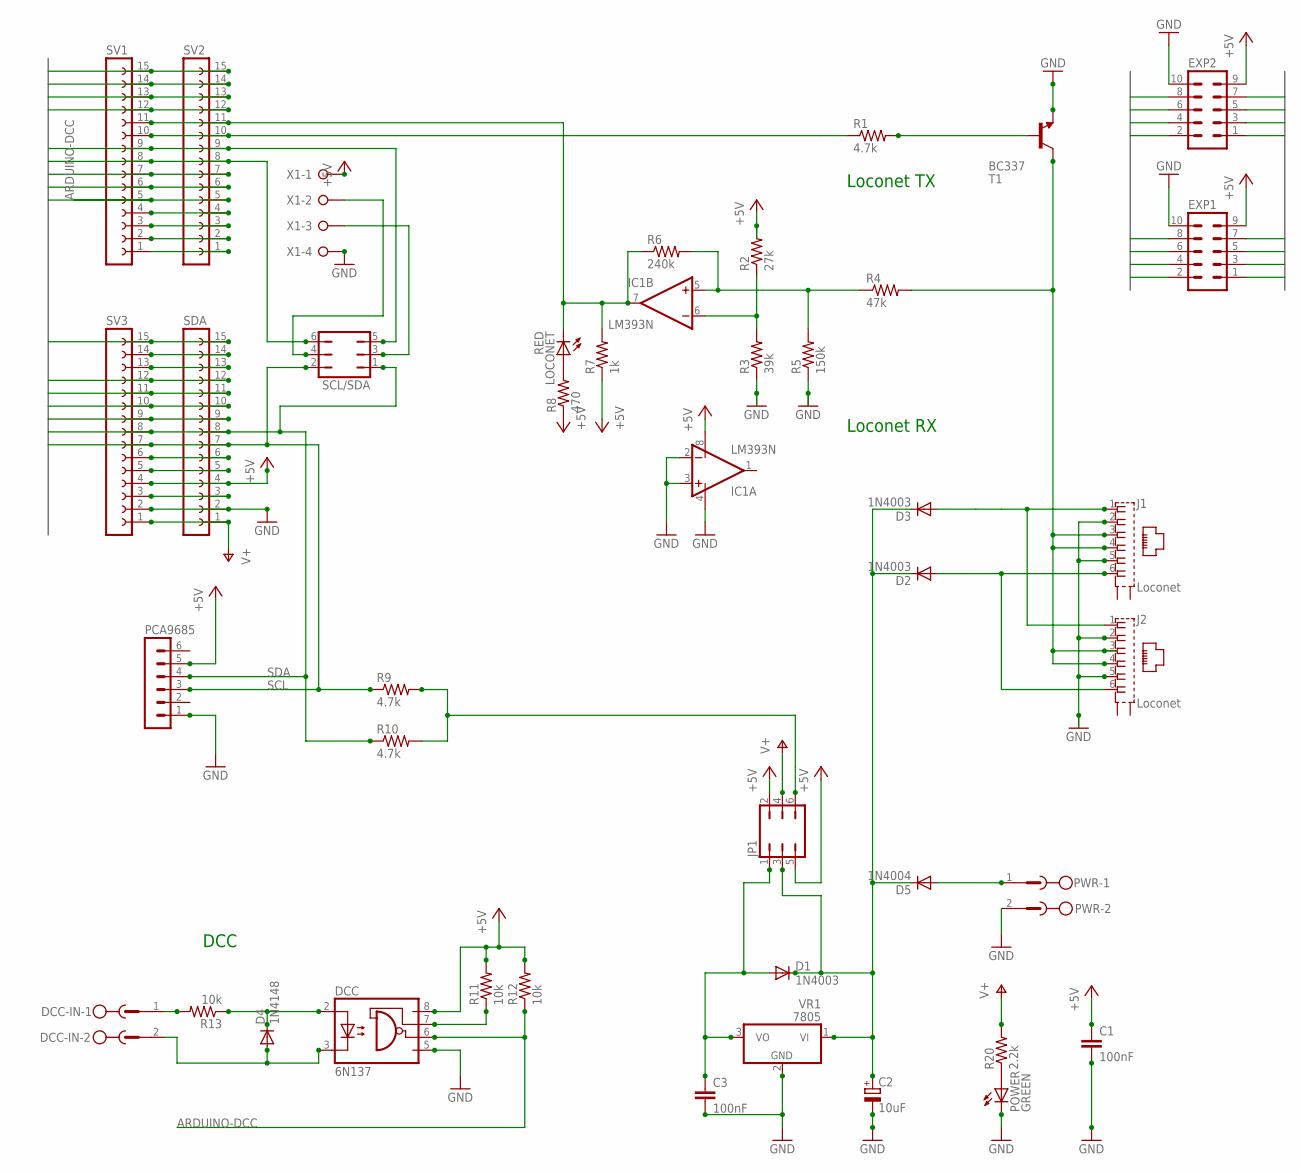
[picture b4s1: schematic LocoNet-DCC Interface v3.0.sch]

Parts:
C1, C3: 100nF; C025_050-025X075
C2: 10uF; E2,5-6
D1, D2, D3: 1N4003; DO41-10
D4: 1N4148; DO35-7
D5: 1N4004; DO41-10
DCC: 6N137; DIL08
DCC-IN: 2EDG-02
EXP1, EXP2: ML10
IC1: LM393N; DIL08
J1, J2: Loconet; 555140-1
JP1: JP3Q
LOCONET: RED; LED3MM
PCA9685: MA06-1
POWER: GREEN; LED3MM
PWR: 2EDG-02
R1, R9, R10: 4.7k; AXIAL-0.3
R2: 27k; AXIAL-0.3
R3: 39k; AXIAL-0.3
R4: 47k; AXIAL-0.3
R5: 150k; AXIAL-0.3
R6: 240k; AXIAL-0.3
R7: 1k; AXIAL-0.3
R8: 470; AXIAL-0.3
R11, R12, R13: 10k; AXIAL-0.3
R20: 2.2k; AXIAL-0.3
SCL/SDA: JP3Q
SDA: FE15-1NOTEXT; FE15
SV1, SV2, SV3: FE15-1NOTEXT; FE15
T1: BC337; TO92
VR1: 7805; TO220V
X1: W237-04P; W237-4P

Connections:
3V3: SDA.14, SV3.14
+5V: C1.1, DCC.8 (VCC), EXP1.9, EXP2.9, IC1.8 (V+), JP1.2, JP1.5, PCA9685.5, R2.P$2 (2), R7.P$1 (1), R8.P$1 (1), R11.P$2 (2), R12.P$2 (2), SDA.4, SV3.4, X1.1
A0: EXP2.3, SDA.12, SV3.12
A1: EXP2.4, SDA.11, SV3.11
A2: EXP2.5, SDA.10, SV3.10
A3: EXP2.6, SDA.9, SV3.9
A6: SDA.6, SV3.6
A7: SDA.5, SV3.5
ARDUINO-DCC: DCC.6 (VO), EXP1.1, R12.P$1 (1), SV1.5, SV2.5
AREF: SDA.13, SV3.13
GND: C1.2, C2.-, C3.2, DCC.5 (GND), EXP1.10, EXP2.10, IC1.2 (-IN), IC1.3 (+IN), IC1.4 (V-), J1.2, J1.5, J2.2, J2.5, PCA9685.1, POWER.K (C), PWR.2, R3.P$1 (1), R5.P$1 (1), SDA.2, SV3.2, T1.1 (E), VR1.2 (GND), X1.4
I2C_PULLUP: JP1.6, R9.P$2 (2), R10.P$2 (2)
L-RX: IC1.7 (OUT), LOCONET.K (C), R6.P$1 (1), R7.P$2 (2), SV1.11, SV2.11
L-TX: R1.P$1 (1), SV1.10, SV2.10
LOCONET-SIGNAL: J1.3, J1.4, J2.3, J2.4, R4.P$2 (2), T1.3 (C)
unnamed: POWER.A, R20.P$1 (1)
unnamed: LOCONET.A, R8.P$2 (2)
unnamed: R1.P$2 (2), T1.2 (B)
unnamed: IC1.6 (-IN), R2.P$1 (1), R3.P$2 (2)
unnamed: IC1.5 (+IN), R4.P$1 (1), R5.P$2 (2), R6.P$2 (2)
unnamed: SDA.3, SV3.3
unnamed: SV1.4, SV2.4
unnamed: D4.C, DCC.2 (A), R13.P$1 (1)
unnamed: D4.A, DCC.3 (C), DCC-IN.2
unnamed: DCC.7 (VE), R11.P$1 (1)
unnamed: DCC-IN.1, R13.P$2 (2)
PIN3: EXP1.2, SV1.6, SV2.6
PIN4: EXP1.3, SV1.7, SV2.7
PIN5: EXP1.4, SCL/SDA.6, SV1.8, SV2.8
PIN6: EXP1.5, SCL/SDA.5, SV1.9, SV2.9
PIN9: EXP1.6, SV1.12, SV2.12
PIN10: EXP1.7, SV1.13, SV2.13
PIN11: EXP1.8, SV1.14, SV2.14
PIN12: EXP2.1, SV1.15, SV2.15
PIN13: EXP2.2, SDA.15, SV3.15
PWR-IN: D5.A, PWR.1
RAILSYNC-A: D3.A, J1.1, J2.1
RAILSYNC-B: D2.A, J1.6, J2.6
RAILSYNC-VIN: C2.+, D1.C, D2.C, D3.C, D5.C, JP1.3, VR1.1 (VI)
RESET: SV1.3, SV2.3
RXD: SV1.2, SV2.2
SCL: EXP2.8, PCA9685.3, R9.P$1 (1), SCL/SDA.2, SDA.7, SV3.7
SDA: EXP2.7, PCA9685.4, R10.P$1 (1), SCL/SDA.1, SDA.8, SV3.8
TXD: SV1.1, SV2.1
V-OUT: C3.1, D1.A, JP1.1, VR1.3 (VO)
VIN: JP1.4, R20.P$2 (2), SDA.1, SV3.1
X1-SCL/D5: SCL/SDA.4, X1.2
X1-SDA/D6: SCL/SDA.3, X1.3

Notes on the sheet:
Loconet RX
Loconet TX
DCC

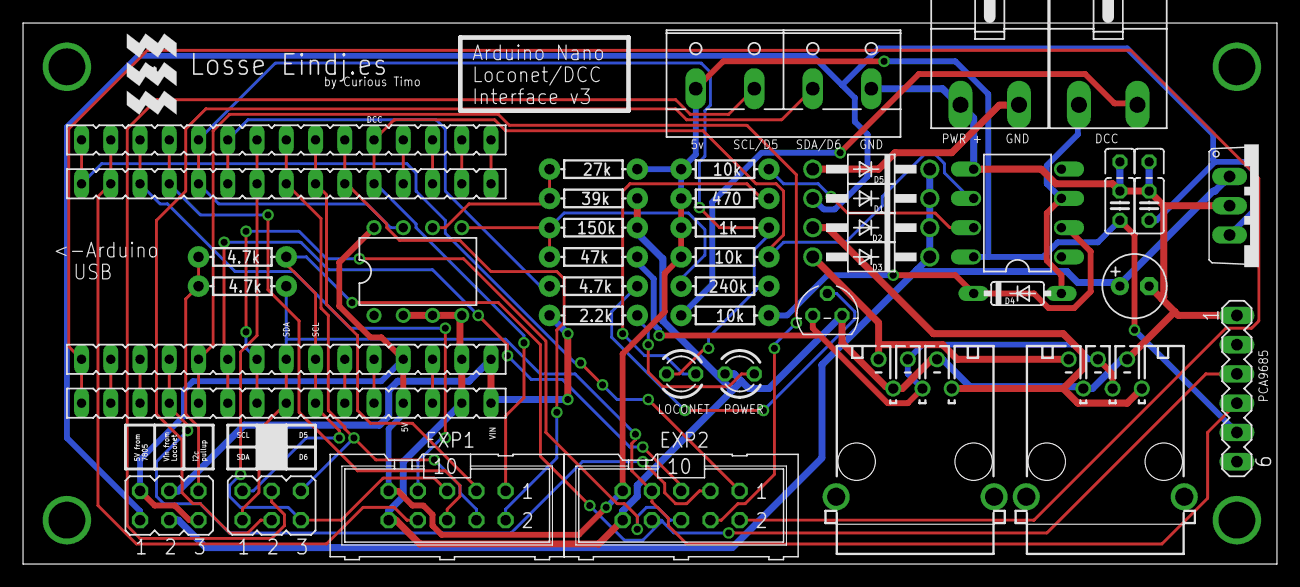
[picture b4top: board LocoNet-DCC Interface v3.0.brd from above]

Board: 2 copper layers, 108.9 x 47.0 mm, 42 parts (0 on the bottom side), 48 nets.

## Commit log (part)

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2018-02-26 Readme Update
    Readme Update
2025-06-29 Update Loconet_Master_Switch.ino
    Code cleanup
2025-06-29 Update LocoNet_Railcom_Display.ino
    Code cleanup and LiquidCrystal_I2C library swap

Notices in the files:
parts and their libraries:
SparkFun-Resistors: Licensing: Creative Commons ShareAlike 4.0 International - https://creativecommons.org/licenses/by-sa/4.0
